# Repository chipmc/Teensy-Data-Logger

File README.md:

# Teensy-Data-Logger
Wi-Fi Connected Teensy Data Logger with GPS and Accelerometer

This is a basic implementation of a Wi-Fi connected data logger.  I used the Teensy 3.1 as the Adafruit Wi-Fi module
requires more SRAM than my Arduino can spare.  I also designed a carrier board for this project and shared both the EAGLE
file as well as the board on OSHPark.  Complete project documentation can be found here: http://triembed.org/blog/?p=959

The device will connect to Wifi, get a GPS fix, and send location information to Ubidots when it detects movement.

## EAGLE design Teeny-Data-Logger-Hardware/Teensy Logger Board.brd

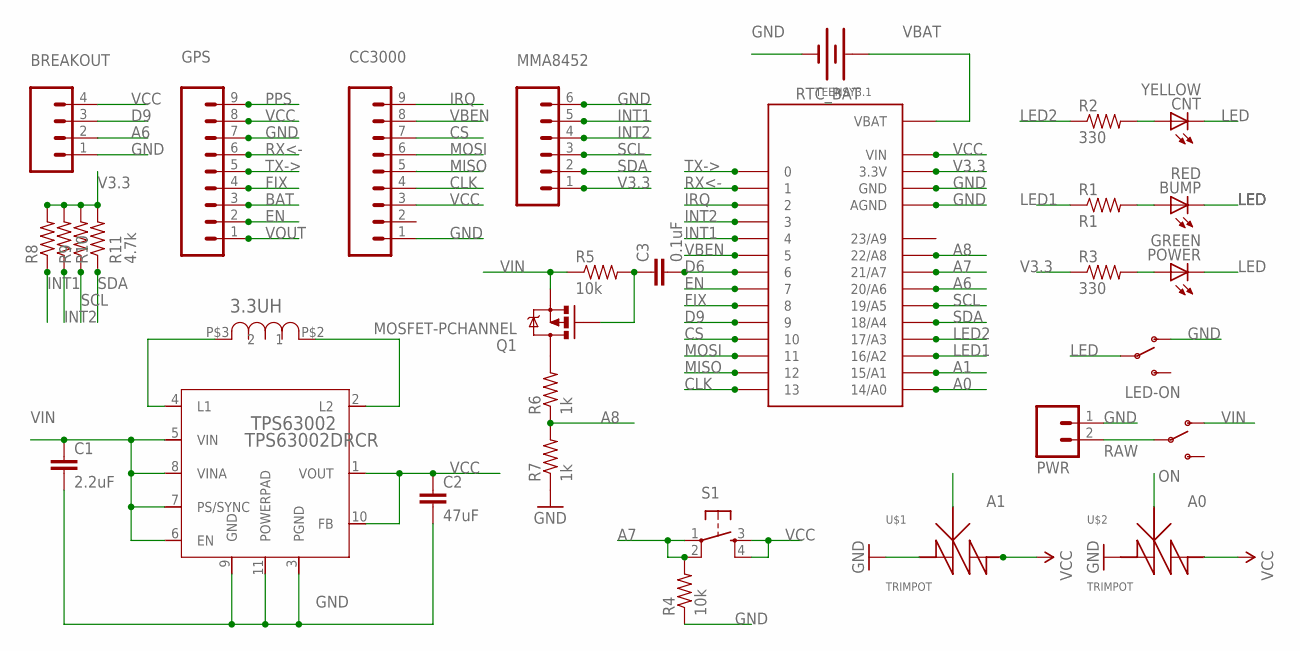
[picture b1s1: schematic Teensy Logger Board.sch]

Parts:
3.3UH: SRR4028; POWERINDUCTOR
BREAKOUT: M04PTH; 1X04
BUMP: RED; CHIP-LED0805
C1: 2.2uF; 1210
C2: 47uF; 0805
C3: 0.1uF; 0805
CC3000: M09; 1X09
CNT: YELLOW; CHIP-LED0805
GPS: M09; 1X09
LED-ON: SWITCH-SPDTPTH; SWITCH-SPDT
MMA8452: M06LOCK; 1X06_LOCK
ON: SWITCH-SPDTPTH; SWITCH-SPDT
POWER: GREEN; CHIP-LED0805
PWR: M02JST-PTH-2; JST-2-PTH
Q1: MOSFET-PCHANNEL; SOT23-3
R1: R1; 0805
R2, R3: 330; 0805
R4, R5: 10k; 0805
R6, R7: 1k; 0805
R8, R9, R10, R11: 4.7k; 0805
RTC_BAT: BATTERY12PTH; BATTCON_12MM_PTH
S1: TAC_SWITCHPTH; TACTILE-PTH
TEENSY3.1: TEENSY_3.1_WIFI
TPS63002: TPS63002DRCR; NEW-S-PVSON-N10
U$1, U$2: TRIMPOT

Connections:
A0: TEENSY3.1.14/A0, U$2.P$1 (VAR)
A1: TEENSY3.1.15/A1, U$1.P$1 (VAR)
A6: BREAKOUT.2, TEENSY3.1.20/A6
A7: R4.2, S1.1, S1.2, TEENSY3.1.21/A7
A8: R6.1, R7.2, TEENSY3.1.22/A8
BAT: GPS.3
CLK: CC3000.4, TEENSY3.1.13
CS: CC3000.7, TEENSY3.1.10
D6: C3.2, TEENSY3.1.6
D9: BREAKOUT.3, TEENSY3.1.9
EN: GPS.2, TEENSY3.1.7
FIX: GPS.4, TEENSY3.1.8
GND: BREAKOUT.1, C1.2, C2.2, CC3000.1, GPS.7, LED-ON.1 (O), MMA8452.6, PWR.1, R4.1, R7.1, RTC_BAT.GND (-), TEENSY3.1.AGND, TEENSY3.1.GND, TPS63002.3 (PGND), TPS63002.9 (GND), TPS63002.11 (POWERPAD), U$1.P$2 (IN), U$2.P$2 (IN)
INT1: MMA8452.5, R8.1, TEENSY3.1.4
INT2: MMA8452.4, R9.1, TEENSY3.1.3
IRQ: CC3000.9, TEENSY3.1.2
LED: BUMP.C, CNT.C, LED-ON.2, POWER.C
LED1: R1.1, TEENSY3.1.16/A2
LED2: R2.1, TEENSY3.1.17/A3
MISO: CC3000.5, TEENSY3.1.12
MOSI: CC3000.6, TEENSY3.1.11
unnamed: CNT.A, R2.2
unnamed: BUMP.A, R1.2
unnamed: POWER.A, R3.2
unnamed: 3.3UH.P$3 (2), TPS63002.4 (L1)
unnamed: 3.3UH.P$2 (1), TPS63002.2 (L2)
unnamed: C3.1, Q1.1 (G), R5.2
unnamed: Q1.3 (D), R6.2
PPS: GPS.9
RAW: ON.2, PWR.2
RX<-: GPS.6, TEENSY3.1.1
SCL: MMA8452.3, R10.1, TEENSY3.1.19/A5
SDA: MMA8452.2, R11.1, TEENSY3.1.18/A4
TX->: GPS.5, TEENSY3.1.0
V3.3: MMA8452.1, R3.1, R8.2, R9.2, R10.2, R11.2, TEENSY3.1.3.3V
VBAT: RTC_BAT.VCC@1 (+), TEENSY3.1.VBAT
VBEN: CC3000.8, TEENSY3.1.5
VCC: BREAKOUT.4, C2.1, CC3000.3, GPS.8, S1.3, S1.4, TEENSY3.1.VIN, TPS63002.1 (VOUT), TPS63002.10 (FB), U$1.P$3 (OUT), U$2.P$3 (OUT)
VIN: C1.1, ON.1 (O), Q1.2 (S), R5.1, TPS63002.5 (VIN), TPS63002.6 (EN), TPS63002.7 (PS/SYNC), TPS63002.8 (VINA)
VOUT: GPS.1

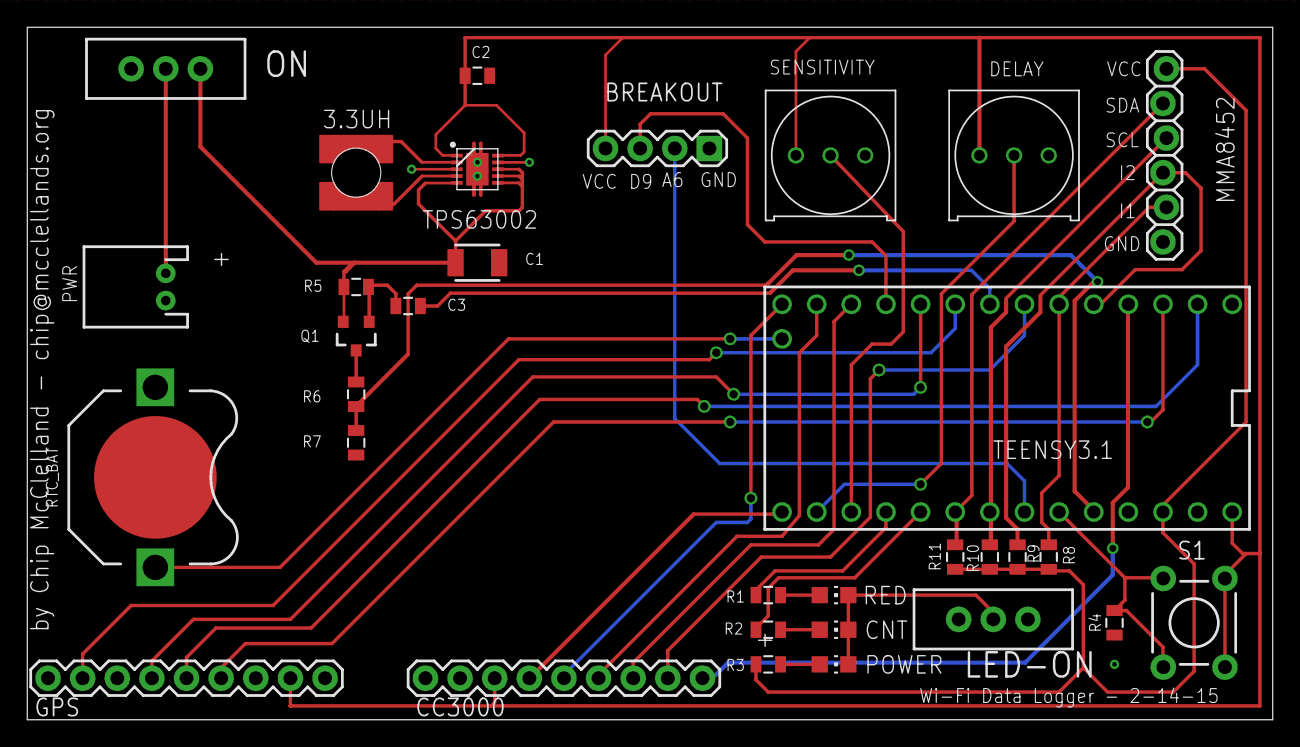
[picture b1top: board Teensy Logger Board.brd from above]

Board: 2 copper layers, 91.4 x 50.8 mm, 32 parts (0 on the bottom side), 37 nets.

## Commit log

2015-03-02 New repository - Basic Code
    This is a starter set of firmware for a connected data logger using the
    Adafruit CC3000 Wi-Fi Module, the Adafruit Ultimate GPS and the
    Sparkfun MMA8452 Accelerometer. More code to write but I wanted to
    share this project at this point to help folks get started.
2015-03-02 Added board pic
2015-03-03 added extension
2015-03-04 changed my float to string approach

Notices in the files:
parts and their libraries:
SparkFun-Connectors: Licensing: CC v3.0 Share-Alike You are welcome to use this library for commercial purposes.
SparkFun-Electromechanical: Licensing: Creative Commons ShareAlike 4.0 International - https://creativecommons.org/licenses/by-sa/4.0
